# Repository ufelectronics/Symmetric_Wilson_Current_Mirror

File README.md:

# Symmetric_Wilson_Current_Mirror
Symmetric_Wilson_Current_Mirror

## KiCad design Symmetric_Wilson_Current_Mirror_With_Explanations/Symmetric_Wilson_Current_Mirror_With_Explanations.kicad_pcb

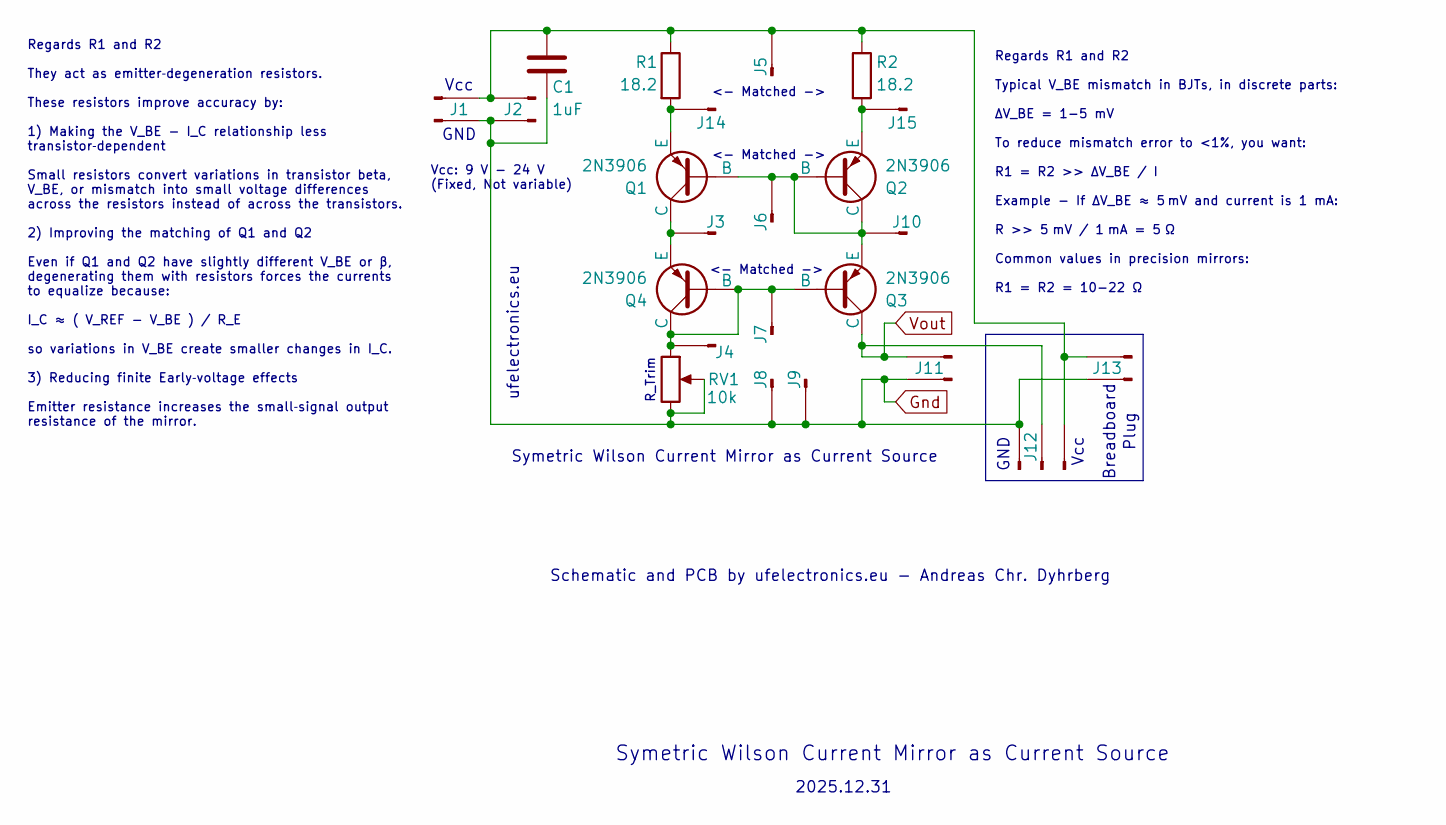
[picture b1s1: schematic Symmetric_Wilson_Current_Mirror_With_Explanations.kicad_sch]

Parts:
C1: 1uF; C_Disc_D7.0mm_W2.5mm_P5.00mm
J1, J2, J11, J13: Conn_01x02_Pin; PinHeader_1x02_P2.54mm_Vertical
J3, J4, J5, J6, J7, J8, J9, J10, J14, J15: Conn_01x01_Pin; PinHeader_1x01_P2.54mm_Vertical
J12: Conn_01x03_Pin; PinHeader_1x03_P2.54mm_Vertical
Q1, Q2, Q3, Q4: 2N3906; TO-92_Inline_Wide
R1, R2: 18.2; R_Axial_DIN0207_L6.3mm_D2.5mm_P10.16mm_Horizontal
RV1: 10k; Potentiometer_Bourns_3296W_Vertical

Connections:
Gnd: C1.2, J1.2, J2.2, J8.1, J9.1, J11.2, J12.3, J13.2, RV1.2, RV1.3
unnamed: C1.1, J1.1, J2.1, J5.1, J12.1, J13.1, R1.1, R2.1
unnamed: J3.1, Q1.1 (C), Q4.3 (E)
unnamed: J4.1, J7.1, Q3.2 (B), Q4.1 (C), Q4.2 (B), RV1.1
unnamed: J6.1, J10.1, Q1.2 (B), Q2.1 (C), Q2.2 (B), Q3.3 (E)
unnamed: J14.1, Q1.3 (E), R1.2
unnamed: J15.1, Q2.3 (E), R2.2
Vout: J11.1, J12.2, Q3.1 (C)

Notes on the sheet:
2025.12.31
<- Matched ->
R_Trim
ufelectronics.eu
Symetric Wilson Current Mirror as Current Source
Plug
Schematic and PCB by ufelectronics.eu - Andreas Chr. Dyhrberg
Vcc
GND
Vcc: 9 V - 24 V (Fixed, Not variable)
Breadboard
Regards R1 and R2 They act as emitter‑degeneration resistors. These resistors improve accuracy by: 1) Making the V_BE - I_C relationship less transistor‑dependent Small resistors convert variations in transistor beta, V_BE, or mismatch into small voltage differences across the resistors instead of 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
Regards R1 and R2 Typical V_BE mismatch in BJTs, in discrete parts: ΔV_BE​​ = 1-5 mV To reduce mismatch error to <1%, you want: R1 = R2 >> ΔV_BE​​ / I Example - If ΔV_BE ≈ 5 mV and current is 1 mA: R >> 5 mV / 1 mA = 5 Ω Common values in precision mirrors: R1 = R2 = 10-22 Ω

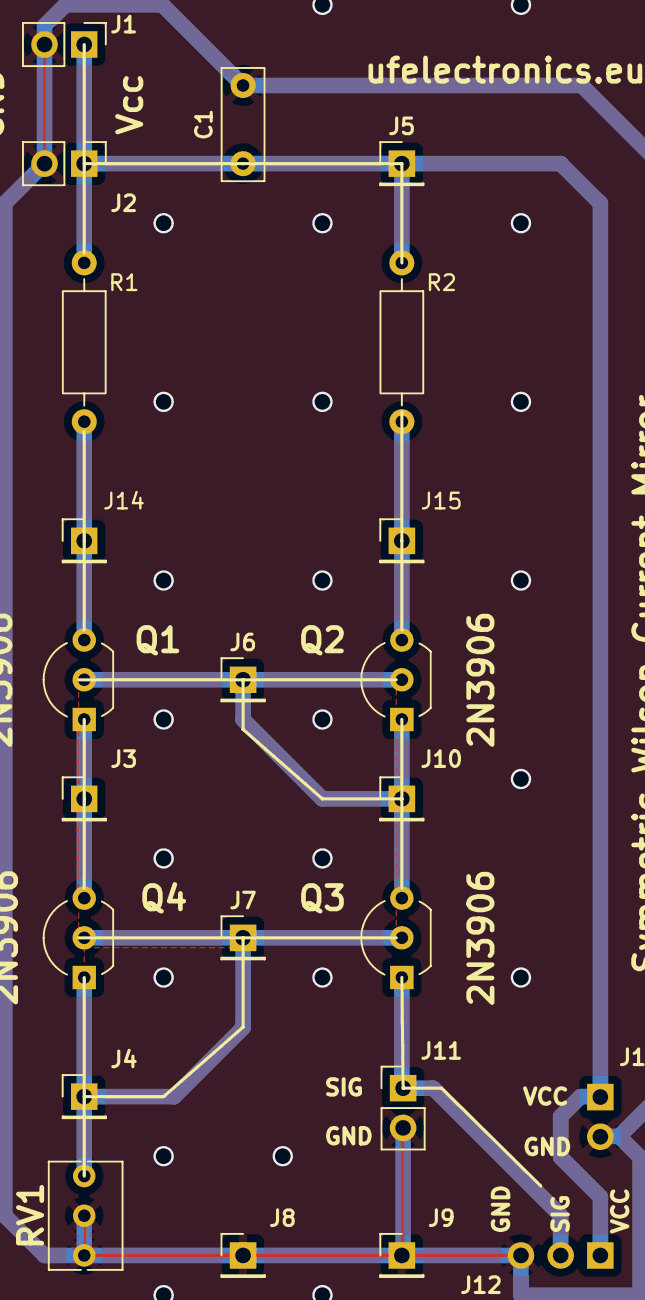
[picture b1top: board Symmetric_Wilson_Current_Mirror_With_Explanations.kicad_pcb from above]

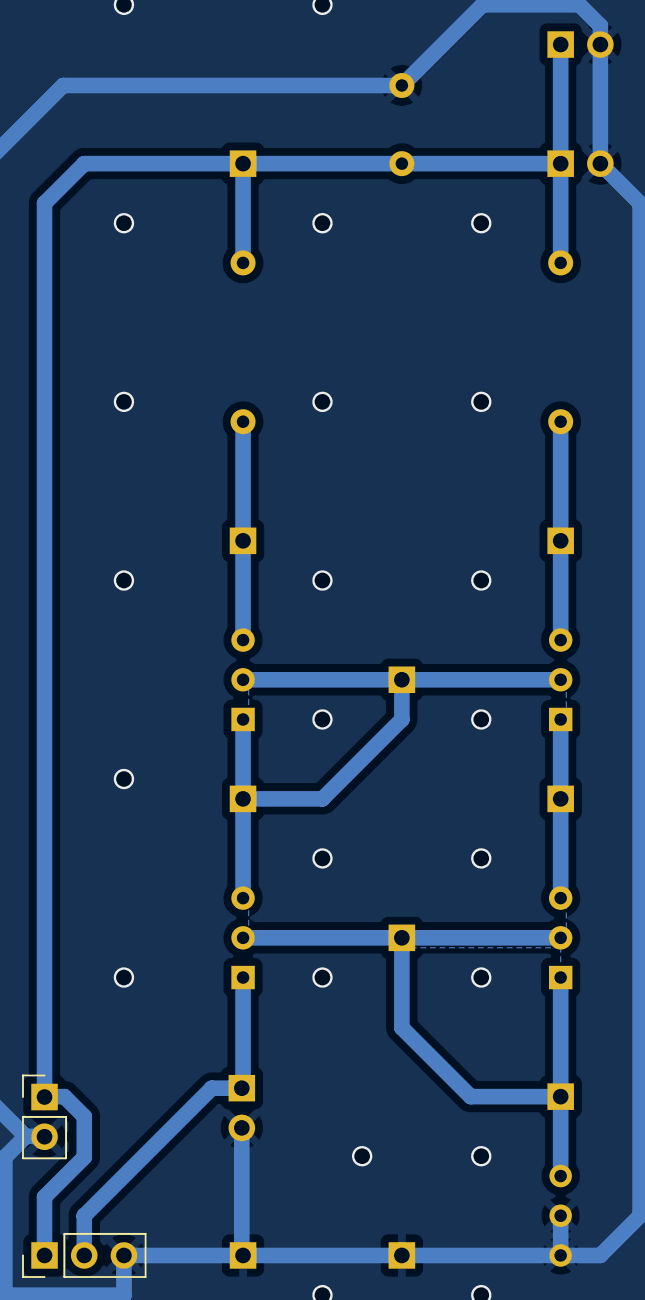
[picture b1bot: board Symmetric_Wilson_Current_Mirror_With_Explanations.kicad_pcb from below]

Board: 2 copper layers, 23 parts (2 on the bottom side), 8 nets.

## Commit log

2025-12-31 Initial Upload
2025-12-31 Added position file for components.
